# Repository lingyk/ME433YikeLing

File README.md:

# ME433YikeLing
Advanced Machatronics

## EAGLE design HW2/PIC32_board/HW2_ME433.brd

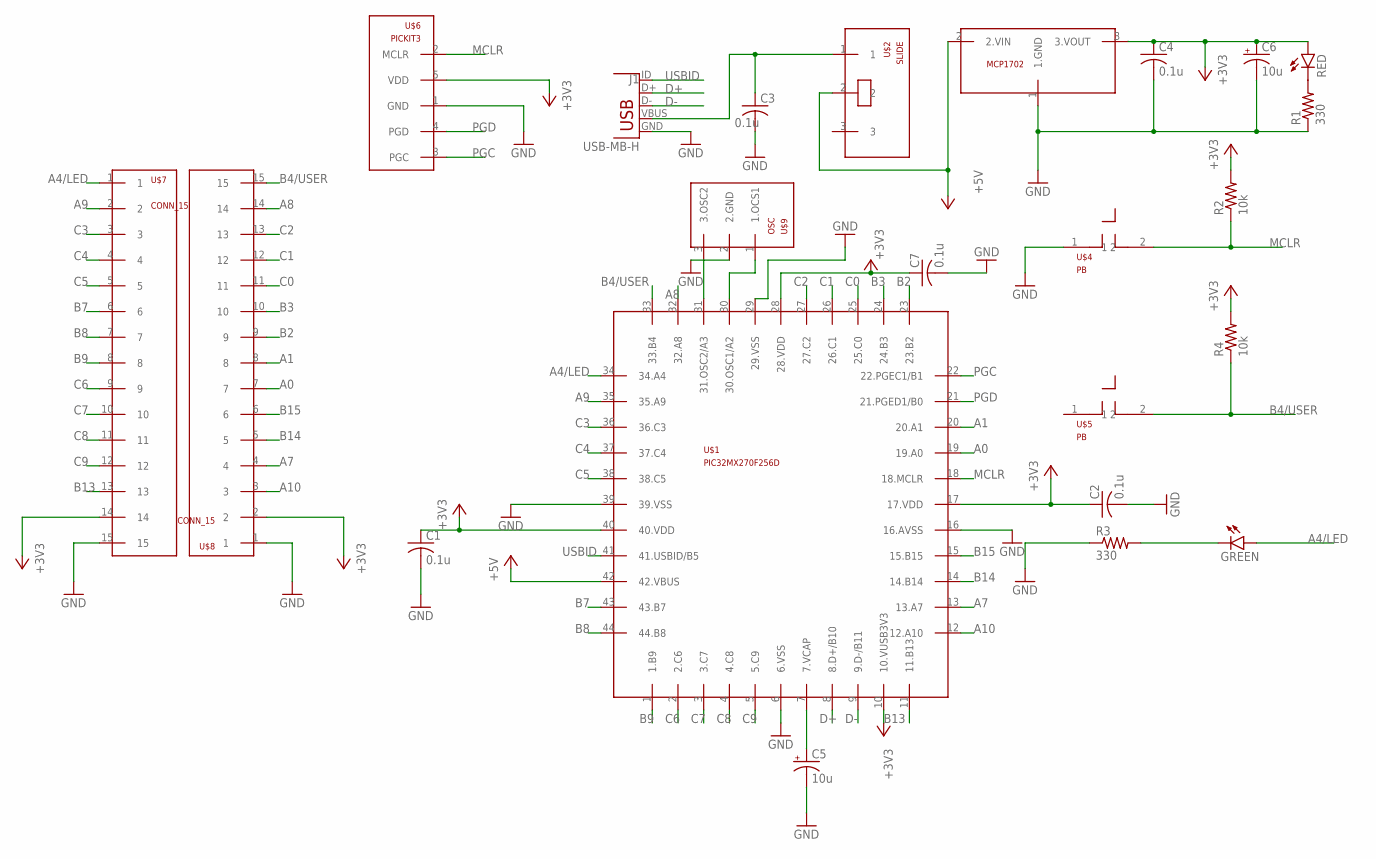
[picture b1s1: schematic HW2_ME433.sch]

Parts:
C1, C2, C3, C4: 0.1u; C025-030X050
C5, C6: 10u; B45181B
C7: 0.1u; C025-025X050
GREEN: LED3MM
J1: USB-MB-H
R1, R3: 330; 0207/10
R2, R4: 10k; 0207/10
RED: LED3MM
U$1: PIC32MX270F256D; TQFP44
U$2: SLIDE
U$3: MCP1702; TO92
U$4, U$5: PB
U$6: PICKIT3; 1X05
U$7, U$8: CONN_15
U$9: OSC

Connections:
+3V3: C1.1, C2.1, C4.1, C6.+, C7.1, R2.2, R4.2, RED.A, U$1.10 (10.VUSB3V3), U$1.17 (17.VDD), U$1.28 (28.VDD), U$1.40 (40.VDD), U$3.3 (3.VOUT), U$6.5 (VDD), U$7.14, U$8.2
+5V: U$1.42 (42.VBUS)
A0: U$1.19 (19.A0), U$8.7
A1: U$1.20 (20.A1), U$8.8
A4/LED: GREEN.A, U$1.34 (34.A4), U$7.1
A7: U$1.13 (13.A7), U$8.4
A8: U$1.32 (32.A8), U$8.14
A9: U$1.35 (35.A9), U$7.2
A10: U$1.12 (12.A10), U$8.3
B2: U$1.23 (23.B2), U$8.9
B3: U$1.24 (24.B3), U$8.10
B4/USER: R4.1, U$1.33 (33.B4), U$5.2, U$8.15
B7: U$1.43 (43.B7), U$7.6
B8: U$1.44 (44.B8), U$7.7
B9: U$1.1 (1.B9), U$7.8
B13: U$1.11 (11.B13), U$7.13
B14: U$1.14 (14.B14), U$8.5
B15: U$1.15 (15.B15), U$8.6
C0: U$1.25 (25.C0), U$8.11
C1: U$1.26 (26.C1), U$8.12
C2: U$1.27 (27.C2), U$8.13
C3: U$1.36 (36.C3), U$7.3
C4: U$1.37 (37.C4), U$7.4
C5: U$1.38 (38.C5), U$7.5
C6: U$1.2 (2.C6), U$7.9
C7: U$1.3 (3.C7), U$7.10
C8: U$1.4 (4.C8), U$7.11
C9: U$1.5 (5.C9), U$7.12
D+: J1.D+, U$1.8 (8.D+/B10)
D-: J1.D-, U$1.9 (9.D-/B11)
GND: C1.2, C2.2, C3.2, C4.2, C5.-, C6.-, C7.2, J1.GND, R1.1, R3.1, U$1.6 (6.VSS), U$1.16 (16.AVSS), U$1.29 (29.VSS), U$1.39 (39.VSS), U$3.1 (1.GND), U$4.1, U$6.1 (GND), U$7.15, U$8.1, U$9.2 (2.GND)
MCLR: R2.1, U$1.18 (18.MCLR), U$4.2, U$6.2 (MCLR)
unnamed: U$1.31 (31.OSC2/A3), U$9.3 (3.OSC2)
unnamed: U$1.30 (30.OSC1/A2), U$9.1 (1.OCS1)
unnamed: GREEN.K (C), R3.2
unnamed: C5.+, U$1.7 (7.VCAP)
unnamed: C3.1, J1.VBUS, U$2.1
unnamed: R1.2, RED.K (C)
PGC: U$1.22 (22.PGEC1/B1), U$6.3 (PGC)
PGD: U$1.21 (21.PGED1/B0), U$6.4 (PGD)
USBID: J1.ID, U$1.41 (41.USBID/B5), U$2.2, U$3.2 (2.VIN)

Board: 2 copper layers, 23 parts (0 on the bottom side), 40 nets, no tracks yet.

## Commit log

2019-04-04 Create HW1
2019-06-14 Create Assemblepic
